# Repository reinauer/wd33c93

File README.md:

# WD33C93 Turbo

Sick of the slow SCSI speed of your Amiga 3000 onboard SCSI? Don't want to
spend the money on an A4091 SCSI controller? Well. Now you can have the cake
and eat it too. With the WD33C93 Turbo Interposer.

Yes, you heard right. This little board sits between your Amiga 3000 mainboard
and your WD33C93 or Am33c93 SCSI chip.

## What's in it?

You can increase the speed of your SCSI device access. On an Amiga 3000 with
25MHz 68030 and a WD33c93 turbo interposer running at 20MHz, we have measured
the following performance with Chris Hooper's devtest (https://github.com/cdhooper/amiga_devtest):

That's a solid 1MB/s more than on a regular Amiga 3000.

## How does it work?

The Amiga 3000 clocks the WD33c93 with 14MHz. Many variants of the chip are
specced for 16 or even 20 MHz.

Instead of feeding the slow 14MHz clock from the mainboard into the SCSI chip,
this little board lets you clock your WD33c93 with the clock frequency it was
designed for. Or a little higher.

## Does this always work?

Probably not. Without a driver update to your scsi.device you even end up with a slightly
overclocked SCSI bus. But your ZuluSCSI 2040 or BlueSCSI v2 does not care. They
can be driven with much higher frequencies that the 5 or 10MHz that the SCSI
bus is normally running at.

What about a real hard drive, you ask? A real CD-ROM? A SCSI attached scanner? I have not
tried. So if you do, please let me know.

## How to build this device?

You need two 20p pin headers, a 40p DIP socket, a 20MHz SMD oscillator (5V
tolerant), a 0.1uF 0805 capacitor and a 1KOhm 0805 Resistor.

## Experimental features

The WD33c93 Turbo can be equipped with two TSSOP DS21S07A active SCSI
terminator chips to add active termination instead of the sub optimal resistor
array based termination on the mainboard. Bonus: This termination can be turned
on/off with a jumper. In addition to the two DS21S07A chips, you will also need
two 4.7uF and one 2.2uF tantalum capacitors (0805) and a 1x02 jumper header.

## Where can I learn more?

Want to learn more about the various types of Wd33c93 and Am33c92 chips?
Check out Chris Hooper's comprehensive comparison at http://eebugs.com/scsi/wd33c93/

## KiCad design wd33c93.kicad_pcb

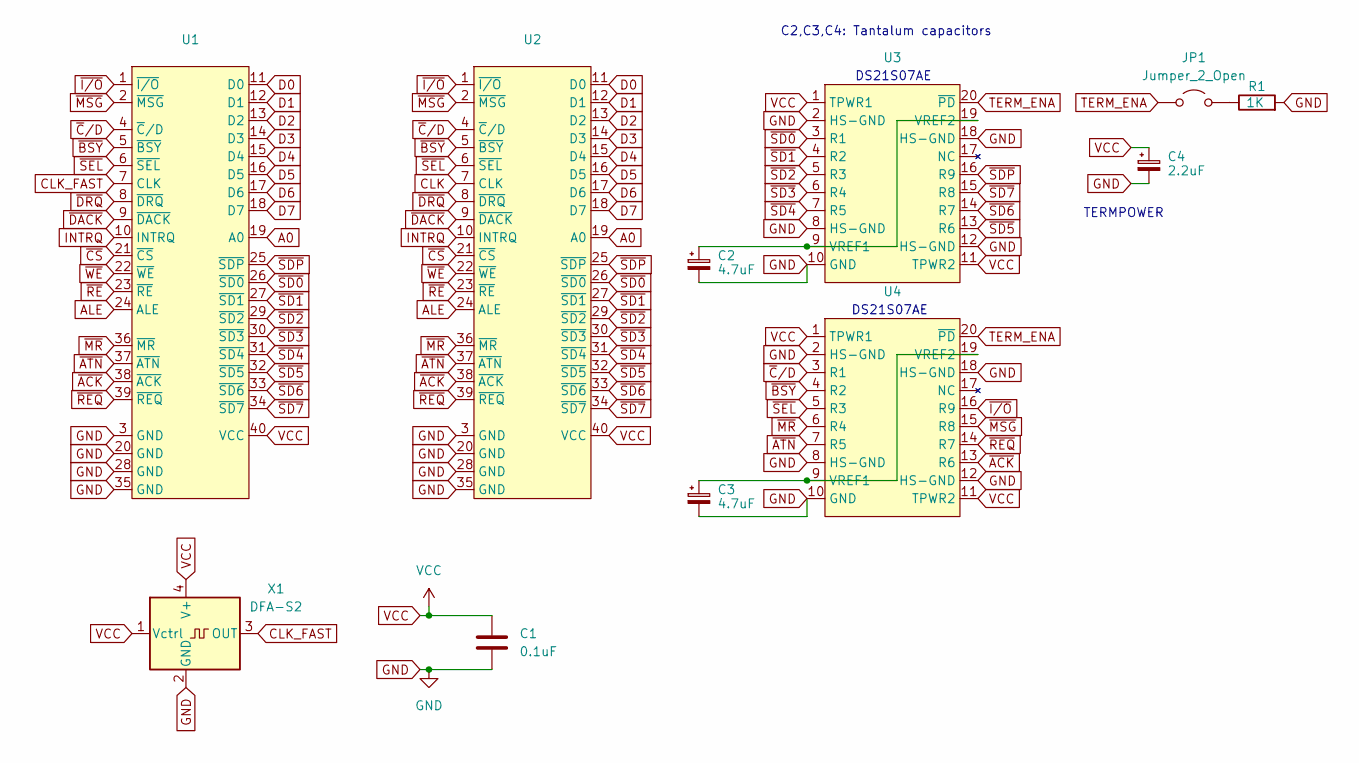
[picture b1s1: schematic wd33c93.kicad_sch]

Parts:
C1: 0.1uF; C_0603_1608Metric
C2, C3: 4.7uF; CP_EIA-2012-12_Kemet-R
C4: 2.2uF; CP_EIA-2012-12_Kemet-R
JP1: Jumper_2_Open; PinHeader_1x02_P2.00mm_Vertical
R1: 1K; R_0805_2012Metric_Pad1.20x1.40mm_HandSolder
U1, U2: DIP-40_W15.24mm_Socket
U3, U4: TSSOP-20_4.4x6.5mm_P0.65mm
X1: DFA-S2; Oscillator_SMD_Fordahl_DFAS2-4Pin_7.3x5.1mm_HandSoldering

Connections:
A0: U1.19 (A0), U2.19 (A0)
ALE: U1.24 (ALE), U2.24 (ALE)
CLK: U2.7 (CLK)
CLK_FAST: U1.7 (CLK), X1.3 (OUT)
D0: U1.11 (D0), U2.11 (D0)
D1: U1.12 (D1), U2.12 (D1)
D2: U1.13 (D2), U2.13 (D2)
D3: U1.14 (D3), U2.14 (D3)
D4: U1.15 (D4), U2.15 (D4)
D5: U1.16 (D5), U2.16 (D5)
D6: U1.17 (D6), U2.17 (D6)
D7: U1.18 (D7), U2.18 (D7)
GND: C1.2, C2.2, C3.2, C4.2, R1.2, U1.3 (GND), U1.20 (GND), U1.28 (GND), U1.35 (GND), U2.3 (GND), U2.20 (GND), U2.28 (GND), U2.35 (GND), U3.2 (HS-GND), U3.8 (HS-GND), U3.10 (GND), U3.12 (HS-GND), U3.18 (HS-GND), U4.2 (HS-GND), U4.8 (HS-GND), U4.10 (GND), U4.12 (HS-GND), U4.18 (HS-GND), X1.2 (GND)
INTRQ: U1.10 (INTRQ), U2.10 (INTRQ)
unnamed: JP1.2 (B), R1.1
unnamed: C2.1, U3.9 (VREF1), U3.19 (VREF2)
unnamed: C3.1, U4.9 (VREF1), U4.19 (VREF2)
TERM_ENA: JP1.1 (A), U3.20 (~PD), U4.20 (~PD)
VCC: C1.1, C4.1, U1.40 (VCC), U2.40 (VCC), U3.1 (TPWR1), U3.11 (TPWR2), U4.1 (TPWR1), U4.11 (TPWR2), X1.1 (Vctrl), X1.4 (V+)
~ACK: U1.38 (~ACK), U2.38 (~ACK), U4.13 (R6)
~ATN: U1.37 (~ATN), U2.37 (~ATN), U4.7 (R5)
~BSY: U1.5 (~BSY), U2.5 (~BSY), U4.4 (R2)
~CS: U1.21 (~CS), U2.21 (~CS)
~C/D: U1.4 (~C/D), U2.4 (~C/D), U4.3 (R1)
~DACK: U1.9 (~DACK), U2.9 (~DACK)
~DRQ: U1.8 (~DRQ), U2.8 (~DRQ)
~I/O: U1.1 (~I/O), U2.1 (~I/O), U4.16 (R9)
~MR: U1.36 (~MR), U2.36 (~MR), U4.6 (R4)
~MSG: U1.2 (~MSG), U2.2 (~MSG), U4.15 (R8)
~REQ: U1.39 (~REQ), U2.39 (~REQ), U4.14 (R7)
~RE: U1.23 (~RE), U2.23 (~RE)
~SD0: U1.26 (~SD0), U2.26 (~SD0), U3.3 (R1)
~SD1: U1.27 (~SD1), U2.27 (~SD1), U3.4 (R2)
~SD2: U1.29 (~SD2), U2.29 (~SD2), U3.5 (R3)
~SD3: U1.30 (~SD3), U2.30 (~SD3), U3.6 (R4)
~SD4: U1.31 (~SD4), U2.31 (~SD4), U3.7 (R5)
~SD5: U1.32 (~SD5), U2.32 (~SD5), U3.13 (R6)
~SD6: U1.33 (~SD6), U2.33 (~SD6), U3.14 (R7)
~SD7: U1.34 (~SD7), U2.34 (~SD7), U3.15 (R8)
~SDP: U1.25 (~SDP), U2.25 (~SDP), U3.16 (R9)
~SEL: U1.6 (~SEL), U2.6 (~SEL), U4.5 (R3)
~WE: U1.22 (~WE), U2.22 (~WE)

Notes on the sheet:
DS21S07AE
C2,C3,C4: Tantalum capacitors
TERMPOWER

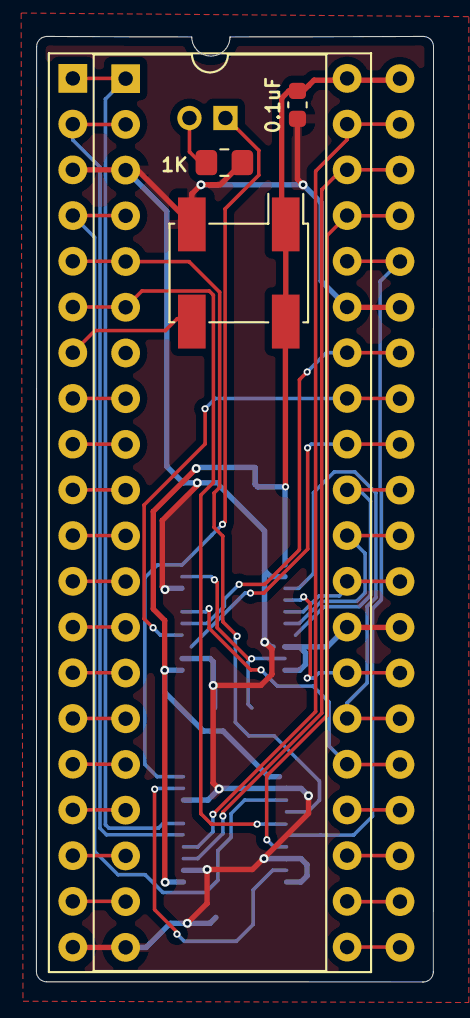
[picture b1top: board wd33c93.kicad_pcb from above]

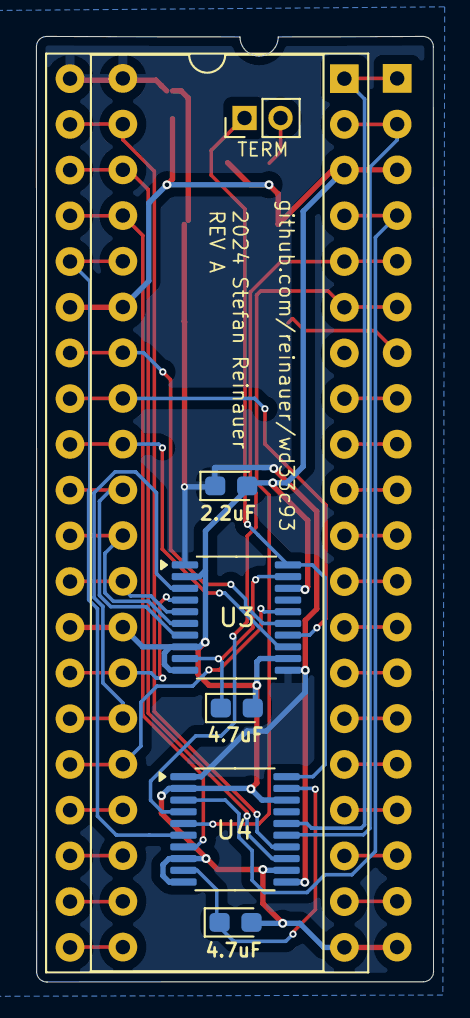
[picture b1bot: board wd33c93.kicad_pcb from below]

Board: 2 copper layers, 22.1 x 52.5 mm, 11 parts (6 on the bottom side), 41 nets.

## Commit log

2024-11-21 Add gerbers
2024-11-21 Fix README.md
2024-11-21 Add picture of PCB
2024-11-21 Minor README fixes
